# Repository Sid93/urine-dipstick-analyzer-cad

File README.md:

# Urine Dipstick Analyzer

> Open-source urine dipstick analyzer using ESP32-S3 + computer vision.

## What it does

A self-contained device that reads off-the-shelf 10-parameter urine dipsticks
(glucose, ketones, bilirubin, blood, pH, protein, urobilinogen, nitrite,
leukocytes, specific gravity) using a calibrated colorimetric pipeline. A
white + UV LED ring illuminates the strip, an OV2640 camera captures the
reaction pads, and an ESP32-S3 runs per-pad ROI analysis against a factory
calibration set anchored to an X-Rite ColorChecker Nano. Results are shown
on a 2.4" ILI9341 display, logged to SD, and optionally streamed over Wi-Fi.
Total BOM is approximately USD 330 in single-unit quantities.

## Photos and drawings

Mechanical drawings (PDF) for every printed/machined part live in
[`drawings/`](drawings/). 3D models in STEP and STL are in the project root
(`im_enclosure_base.*`, `enclosure_cover.*`, `camera_led_mount.*`,
`scanner_mount.*`, `vent_grill.*`, `im_tray.*`, `internal_wire_frame.*`).
Schematic render: [`schematic_render.png`](schematic_render.png).

## Hardware overview

| Subsystem | Part | Notes |
|---|---|---|
| MCU | ESP32-S3-DevKitC-1-N8R8 | 8 MB flash, 8 MB OPI PSRAM, dual-core |
| Camera | OV2640 (DVP) | hardware DVP on ESP32-S3 |
| Display | 2.4" ILI9341 SPI TFT | 320 x 240, Adafruit_ILI9341 driver |
| Illumination | White + 365 nm UV LEDs | constant-current via PMOS |
| Strip transport | NEMA-8 stepper + A4988 | AccelStepper-driven |
| Environment | SHT31 (T/RH), BH1750 (lux), DS3231 (RTC) | I2C bus |
| Power | Single 18650 + MCP73833 charger + MAX17048 fuel gauge | 3.7 V Li-ion |
| Enclosure | FDM PETG, M2.5 fasteners | STEP files in repo root |
| BOM cost | ~USD 330 | single-unit, see `BOM.csv` |

## Repository structure

```
.
├── README.md                      this file
├── LICENSE                        MIT
├── ASSEMBLY_GUIDE.md              SMT solder order, harnesses, mech build
├── BUILD_REPORT.md / _v2.md       generation pass logs
├── BOM.csv / BOM.pdf              bill of materials with MPNs
├── calibration.json               factory calibration (10 pads, 24-patch ref)
├── urine_dipstick_analyzer.*      KiCad project (sch + pcb + pro)
├── schematic_render.png           SVG-rendered schematic preview
├── generate_*.py                  reproducible build scripts (sch/pcb/cad/bom/drawings)
├── route_pcb.py                   programmatic auto-router for PCB1
├── drawings/                      mechanical PDFs
├── gerbers/                       fab-ready gerbers + drill (PCB1)
├── gerbers.zip                    zipped fab package
├── firmware/urine_dipstick_analyzer/   PlatformIO project + .ino + .h modules
├── *.step / *.stl                 mechanical 3D models (7 parts)
```

## Quick start

```bash
# 1. Clone
git clone https://github.com/Sid93/urine-dipstick-analyzer-cad.git
cd urine-dipstick-analyzer-cad

# 2. Install PlatformIO
pip3 install --user platformio

# 3. Build and flash the ESP32-S3
cd firmware/urine_dipstick_analyzer
pio run -t upload
pio device monitor
```

## Build the prototype

Full step-by-step build instructions live in two documents:

- [`BUILD_REPORT.md`](BUILD_REPORT.md) — design rationale, optical/colorimetric
  pipeline, per-subsystem reasoning.
- [`ASSEMBLY_GUIDE.md`](ASSEMBLY_GUIDE.md) — SMT solder order with bring-up
  tests, harness diagrams, mechanical assembly order, first-boot checklist,
  troubleshooting matrix.

## Project status

What works:

- Schematic and BOM are complete with manufacturer part numbers.
- PCB1 (power-distribution hub) is laid out, programmatically routed, and
  fab-ready gerbers are in `gerbers/`.
- Firmware compiles for ESP32-S3 (PlatformIO project, modular `.h` headers).
- Mechanical CAD is complete (STEP + STL for all 7 parts) with PDF drawings.
- Calibration JSON includes a full 24-patch ColorChecker reference and
  per-pad polynomial coefficients.

What is incomplete or known-issue:

- The PCB router is a simple Manhattan-MST router with naive crossing
  detection — it produces a manufacturable layout but not an optimized one.
  Recommend a manual review pass in KiCad and DRC run before fabricating.
- A few GPIO collisions in `firmware/urine_dipstick_analyzer/config.h` were
  flagged in v2 build report; some are now fixed in commit c849104 but a
  full strapping-pin audit is still recommended.
- Calibration values are realistic placeholders. The in-firmware
  `/calibrate` routine MUST be re-run with a real ColorChecker Nano under
  integrated illumination before any meaningful measurement.
- No clinical validation has been performed.

## Regulatory disclaimer

**This device is for research and educational use only. It is NOT a medical
device. It has not been evaluated or cleared by the U.S. FDA, the European
CE/IVDR process, or India's CDSCO.** In India, any in-vitro diagnostic
device intended for sale or clinical use requires CDSCO approval under the
Medical Devices Rules, 2017. Equivalent regulation applies in every other
jurisdiction. Do not use the output of this device to make clinical or
treatment decisions for yourself or anyone else. The authors and
contributors accept no liability for any use of this hardware or software.

## License

This project is licensed under the [MIT License](LICENSE).

## Citation

If you use this work in academic publications, please cite:

```bibtex
@misc{saboo2026urinedipstick,
  author       = {Saboo, Siddhant},
  title        = {Open-source Urine Dipstick Analyzer (ESP32-S3 + Computer Vision)},
  year         = {2026},
  howpublished = {\url{https://github.com/Sid93/urine-dipstick-analyzer-cad}},
  note         = {Research prototype, not a medical device}
}
```

## Acknowledgments

Built with the open-source ecosystem: KiCad 10, PlatformIO, the Espressif
Arduino core, Adafruit's GFX/ILI9341/BusIO/SHT31 libraries, Mike McCauley's
AccelStepper, Christopher Laws's BH1750 driver, Benoit Blanchon's
ArduinoJson, the X-Rite ColorChecker reference data, and Anthropic's
Claude for the agentic generation passes that produced the CAD, schematic,
PCB, gerbers, BOM, drawings, firmware scaffolding, and assembly guide.

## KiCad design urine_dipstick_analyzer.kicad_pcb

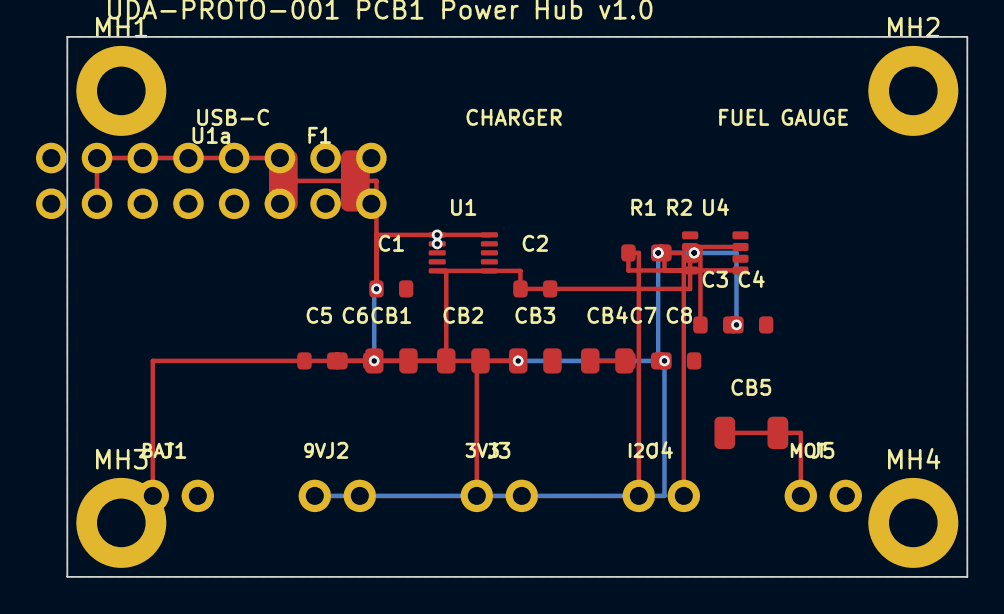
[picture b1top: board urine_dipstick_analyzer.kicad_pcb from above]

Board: 2 copper layers, 50.0 x 30.0 mm, 28 parts (0 on the bottom side), 10 nets.

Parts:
C1, C2, C3, C4, C5, C6, C7, C8: 100nF; C_0603_1608Metric
CB1, CB2, CB3, CB4: 10uF; C_0805_2012Metric
CB5: 100uF; C_1206_3216Metric
F1: 500mA_PTC; Fuse_1812_4532Metric
J1: BAT; JST_XH_B2B-XH-A_1x02_P2.50mm_Vertical
J2: 9V_OUT; JST_XH_B2B-XH-A_1x02_P2.50mm_Vertical
J3: 3V3_OUT; JST_XH_B2B-XH-A_1x02_P2.50mm_Vertical
J4: I2C_BUS; JST_XH_B2B-XH-A_1x02_P2.50mm_Vertical
J5: MOTOR_PWR; JST_XH_B2B-XH-A_1x02_P2.50mm_Vertical
MH1, MH2, MH3, MH4: MountingHole; MountingHole_2.7mm_M2.5
R1, R2: 4.7k; R_0603_1608Metric
U1: MCP73833; MSOP-10_3x3mm_P0.5mm
U1a: USB-C-BO; PinHeader_2x08_P2.54mm_Vertical
U4: MAX17048; SOT-23-8

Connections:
+3V3: C4.1, C6.1, CB3.1, J3.1, R1.2, R2.2
+5V: C7.1, CB4.1
+9V: C8.1, J2.1
CHRG_STAT: U1.1, U1.2
GND: C1.2, C2.2, C3.2, C4.2, C5.2, C6.2, C7.2, C8.2, CB1.2, CB2.2, CB3.2, CB4.2, CB5.2, J1.2, J2.2, J3.2, J5.2, U1.4, U1.7, U1.8, U1.9, U1a.1, U1a.2, U4.1, U4.3
SCL: J4.2, R2.1, U4.5
SDA: J4.1, R1.1, U4.4
VBAT: C2.1, C3.1, C5.1, CB2.1, J1.1, U1.5, U1.6, U4.2, U4.7
VBUS: C1.1, CB1.1, F1.1, F1.2, U1.10, U1a.3, U1a.4
VMOT: CB5.1, J5.1

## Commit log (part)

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2026-05-16 Add prototype assets: PCB, gerbers, PlatformIO, calibration, assembly guide
    - generate_pcb.py: programmatic KiCad 10 PCB generator for the 50x30mm
    power-distribution board (PCB1) with footprints, mounting holes, GND
    zones on both layers. Routing left to user.
    - urine_dipstick_analyzer.kicad_pcb: generated PCB (unrouted).
    - gerbers/ + gerbers.zip: kicad-cli exported gerbers + drill, fab-ready
    once the user hand-routes the remaining nets.
2026-05-16 Route PCB, add README+LICENSE, verify firmware build
2026-05-16 Add CDSCO MDR 2017 Class B regulatory dossier
2026-05-16 Add ESP32+BH1750 production-grade reference design
    A complete USB-C powered ESP32-WROOM-32E + BH1750FVI ambient light sensor
    reference design that demonstrates proper EE practices: USB-C protection
    stack (USBLC6 ESD, SMAJ5.0 TVS, polyfuse, AO3401A reverse-polarity PMOS),
    AMS1117-3.3 LDO with 22uF/100nF input+output decoupling, BLM18PG121
    ferrite bead feeding a clean ESP32 VDD33 rail, correct boot strapping
    (GPIO0 PU+button, GPIO2 PD, GPIO15 PU), EN reset RC (10k+100nF, 1ms tau),
2026-05-16 Document USB-CDC and OPI PSRAM hardware conflicts with 3 resolution paths
2026-05-16 Add GitHub Actions CI: auto-build firmware on push
    Runs pio build on Ubuntu for ESP32-S3-DevKitC-1 on every push that
    touches firmware/. Caches the PlatformIO toolchain (~600 MB) to keep
    subsequent runs under 90 seconds. Uploads firmware.bin as a 30-day
    artifact for easy flashing.
    Catches regressions in pin assignments, library bumps, and config
    changes without needing local PIO setup.
